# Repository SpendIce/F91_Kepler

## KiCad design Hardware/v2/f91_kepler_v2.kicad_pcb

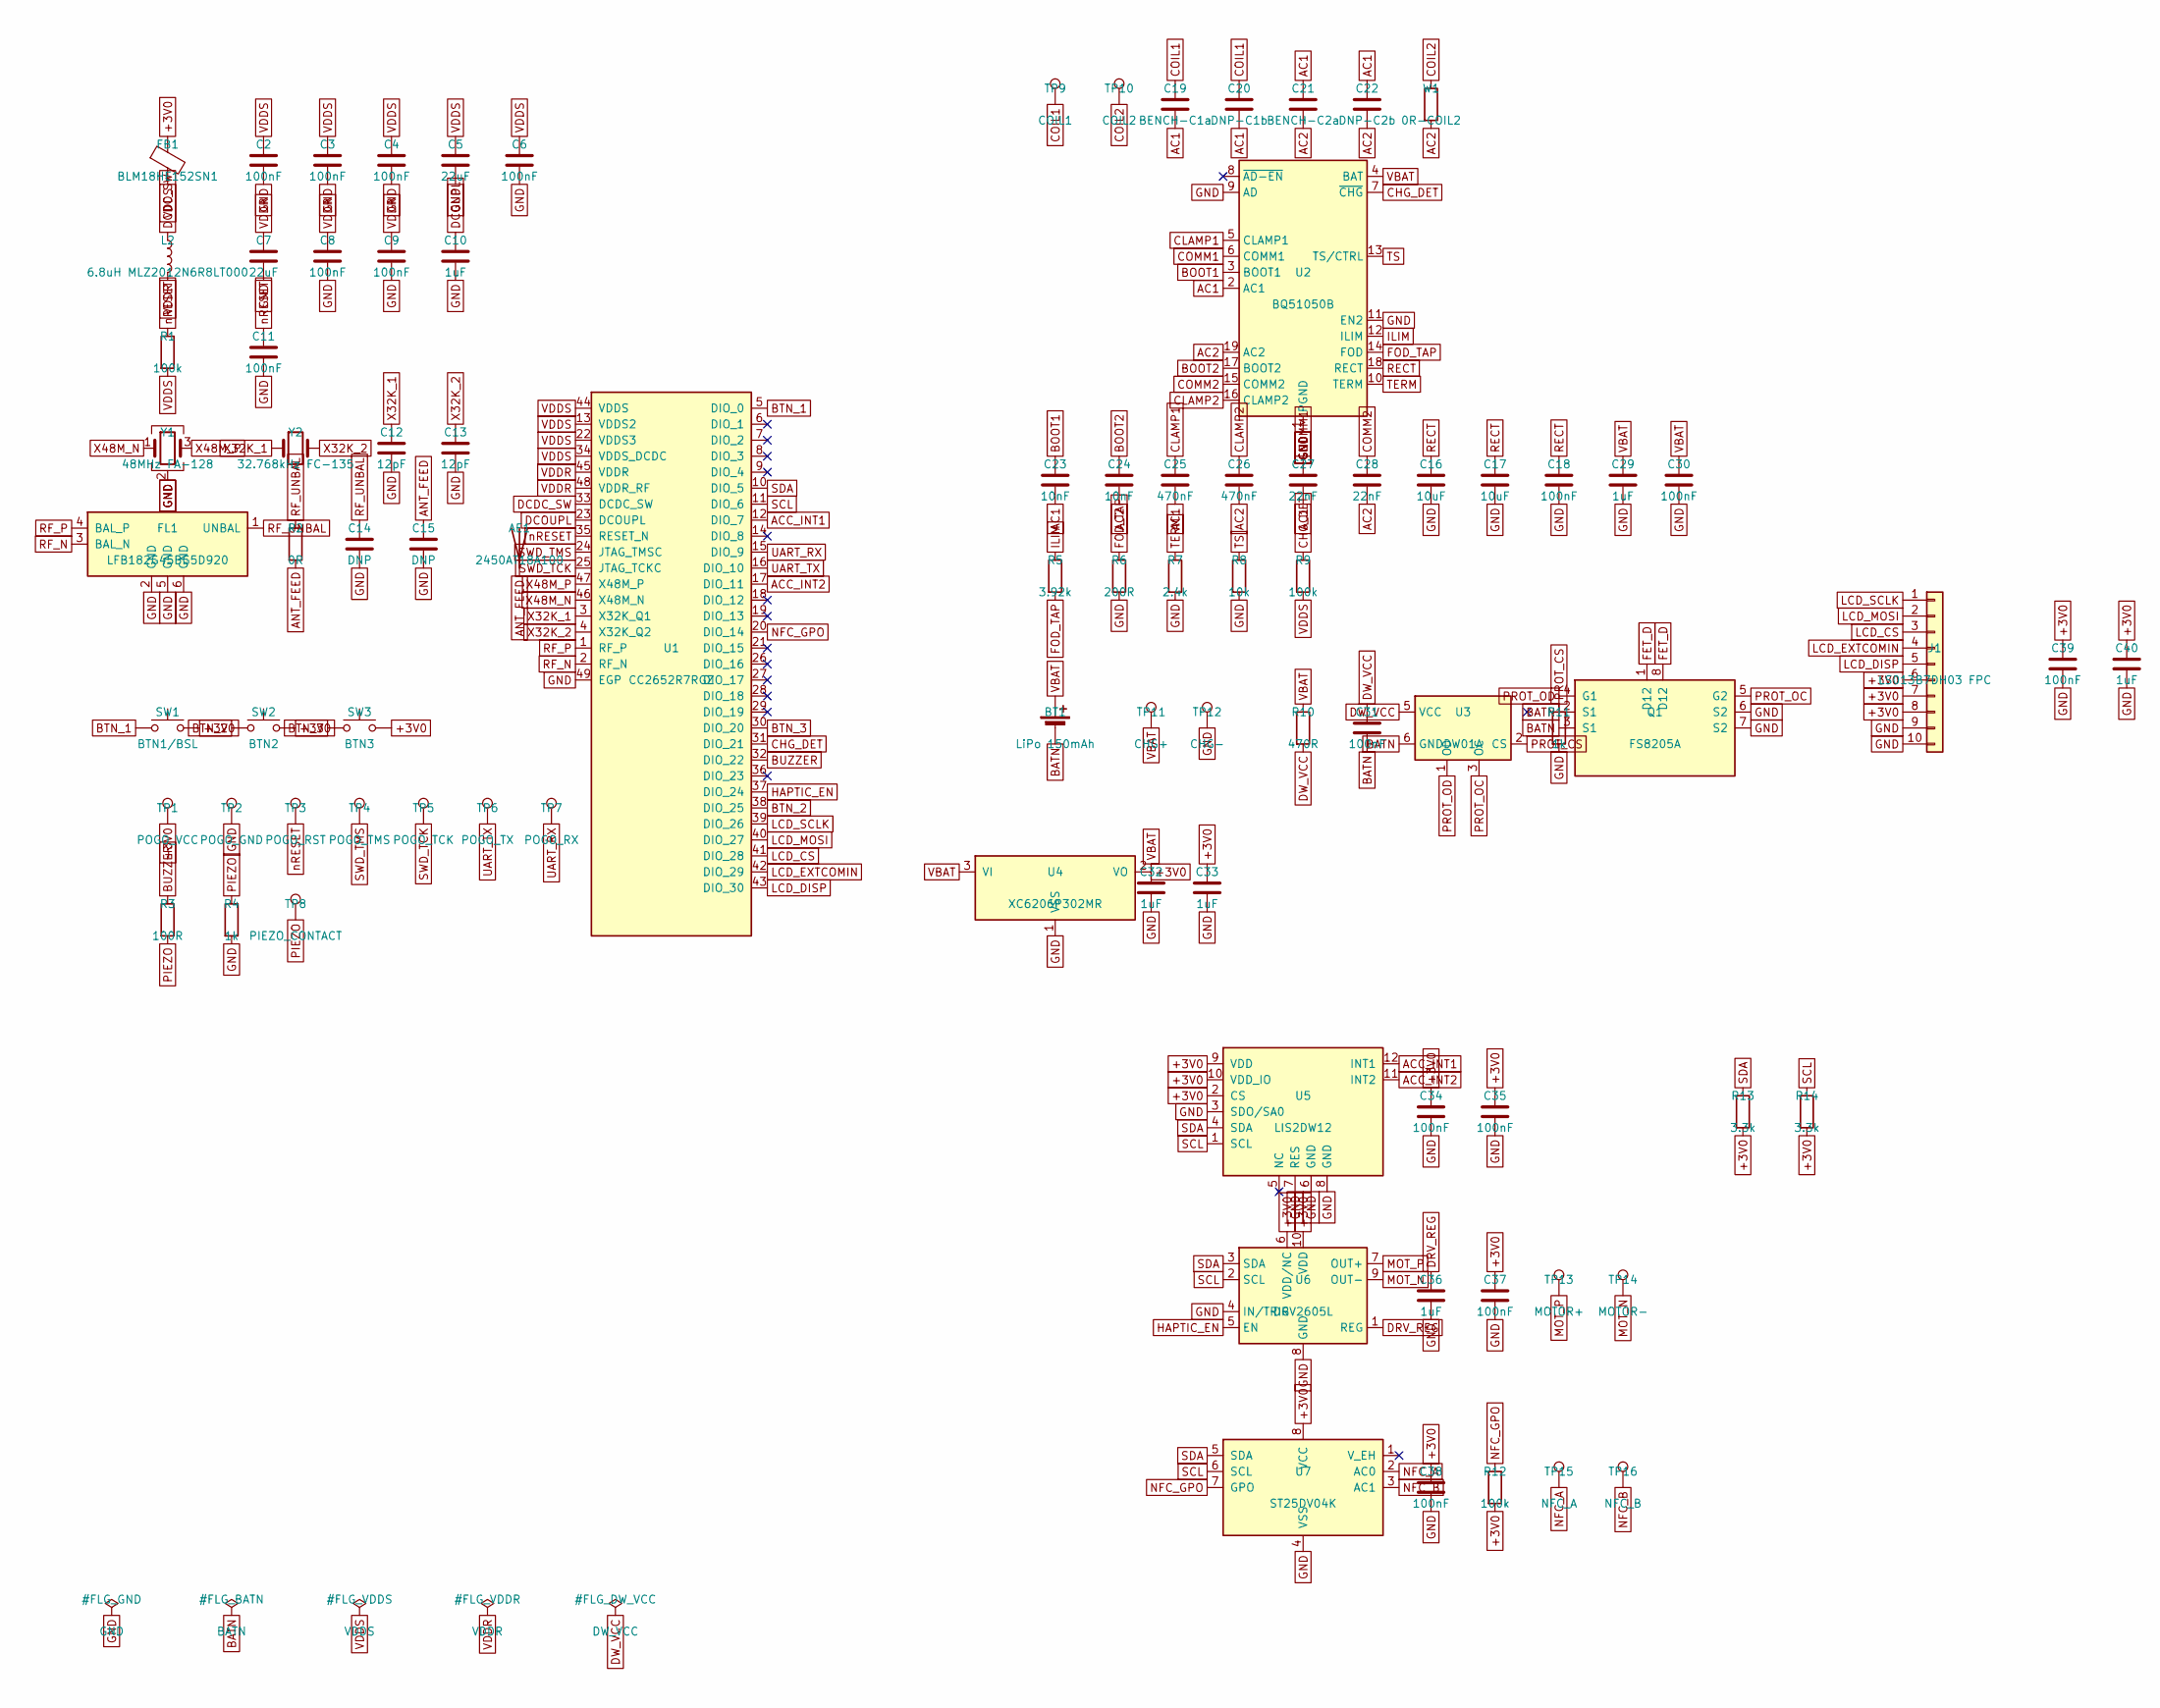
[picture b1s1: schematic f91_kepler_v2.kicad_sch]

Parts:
AE1: 2450AT18A100; ANT_2450AT18A100
BT1: LiPo 150mAh; Back_BatteryPads
C2, C3, C4, C6, C8, C9, C11, C34, C35, C39: 100nF; C_0402_1005Metric
C5, C7: 22uF; C_0603_1608Metric
C10, C40: 1uF; C_0402_1005Metric
C12, C13: 12pF; C_0402_1005Metric
C14, C15: DNP; C_0402_1005Metric
C16, C17: 10uF; Back_C_0603_1608Metric
C18, C30, C31, C37, C38: 100nF; Back_C_0402_1005Metric
C19: BENCH-C1a; Back_C_0603_1608Metric
C20: DNP-C1b; Back_C_0603_1608Metric
C21: BENCH-C2a; Back_C_0402_1005Metric
C22: DNP-C2b; Back_C_0402_1005Metric
C23, C24: 10nF; Back_C_0402_1005Metric
C25, C26: 470nF; Back_C_0402_1005Metric
C27, C28: 22nF; Back_C_0402_1005Metric
C29, C32, C33, C36: 1uF; Back_C_0402_1005Metric
FB1: BLM18HE152SN1; L_0603_1608Metric
FL1: LFB182G45BG5D920; F91_Murata_LFB18_1608
J1: LS013B7DH03 FPC; F91_LCD_FPC_Hirose_FH12-10
L2: 6.8uH MLZ2012N6R8LT000; L_0805_2012Metric
Q1: FS8205A; Back_TSSOP-8_3x3mm_P0.65mm
R1, R9: 100k; R_0402_1005Metric
R2: 0R; R_0402_1005Metric
R3: 100R; R_0402_1005Metric
R4: 1k; R_0402_1005Metric
R5: 3.92k; Back_R_0402_1005Metric
R6: 200R; Back_R_0402_1005Metric
R7: 2.4k; Back_R_0402_1005Metric
R8: 10k; Back_R_0402_1005Metric
R10: 470R; Back_R_0402_1005Metric
R11: 1k; Back_R_0402_1005Metric
R12: 100k; Back_R_0402_1005Metric
R13, R14: 3.3k; Back_R_0402_1005Metric
SW1: BTN1/BSL; SW_Push_1P1T_NO_CK_KMR2
SW2: BTN2; SW_Push_1P1T_NO_CK_KMR2
SW3: BTN3; SW_Push_1P1T_NO_CK_KMR2
TP1: POGO_VCC; Back_TestPoint_Pad_1.5x1.5mm
TP2: POGO_GND; Back_TestPoint_Pad_1.5x1.5mm
TP3: POGO_RST; Back_TestPoint_Pad_1.5x1.5mm
TP4: POGO_TMS; Back_TestPoint_Pad_1.5x1.5mm
TP5: POGO_TCK; Back_TestPoint_Pad_1.5x1.5mm
TP6: POGO_TX; Back_TestPoint_Pad_1.5x1.5mm
TP7: POGO_RX; Back_TestPoint_Pad_1.5x1.5mm
TP8: PIEZO_CONTACT; Back_TestPoint_Pad_1.5x1.5mm
TP9: COIL1; Back_TestPoint_Pad_1.5x1.5mm
TP10: COIL2; Back_TestPoint_Pad_1.5x1.5mm
TP11: CHG+; Back_TestPoint_Pad_1.5x1.5mm
TP12: CHG-; Back_TestPoint_Pad_1.5x1.5mm
TP13: MOTOR+; Back_TestPoint_Pad_1.5x1.5mm
TP14: MOTOR-; Back_TestPoint_Pad_1.5x1.5mm
TP15: NFC_A; Back_TestPoint_Pad_1.5x1.5mm
TP16: NFC_B; Back_TestPoint_Pad_1.5x1.5mm
U1: CC2652R7RGZ; QFN-48-1EP_7x7mm_P0.5mm_EP5.15x5.15mm
U2: BQ51050B; Back_VQFN-20-1EP_4.5x3.5mm_P0.5mm
U3: DW01A; Back_SOT-23-6
U4: XC6206P302MR; Back_SOT-23
U5: LIS2DW12; LGA-12_2x2mm_P0.5mm
U6: DRV2605L; Back_VSSOP-10_3x3mm_P0.5mm
U7: ST25DV04K; Back_SOIC-8_3.9x4.9mm_P1.27mm
W1: 0R-COIL2; Back_R_0402_1005Metric
Y1: 48MHz FA-128; Epson_FA-128_2.0x1.6mm
Y2: 32.768kHz FC-135; Crystal_SMD_3215-2Pin_3.2x1.5mm

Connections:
+3V0: C33.1, C34.1, C35.1, C37.1, C38.1, C39.1, C40.1, FB1.1, J1.6, J1.7, J1.8, R12.2, R13.2, R14.2, SW1.2, SW2.2, SW3.2, TP1.1, U4.2 (VO), U5.2 (CS), U5.9 (VDD), U5.10 (VDD_IO), U6.6 (VDD/NC), U6.10 (VDD), U7.8 (VCC)
AC1: C19.2, C20.2, C21.1, C22.1, C23.2, C25.2, C27.2, U2.2 (AC1)
AC2: C21.2, C22.2, C24.2, C26.2, C28.2, U2.19 (AC2), W1.2
ACC_INT1: U1.12 (DIO_7), U5.12 (INT1)
ACC_INT2: U1.17 (DIO_11), U5.11 (INT2)
ANT_FEED: AE1.1, C15.1, R2.2
BATN: BT1.2 (-), C31.2, Q1.2 (S1), Q1.3 (S1), U3.6 (GND)
BOOT1: C23.1, U2.3 (BOOT1)
BOOT2: C24.1, U2.17 (BOOT2)
BTN_1: SW1.1, U1.5 (DIO_0)
BTN_2: SW2.1, U1.38 (DIO_25)
BTN_3: SW3.1, U1.30 (DIO_20)
BUZZER: R3.1, U1.32 (DIO_22)
CHG_DET: R9.1, U1.31 (DIO_21), U2.7 (~CHG)
CLAMP1: C25.1, U2.5 (CLAMP1)
CLAMP2: C26.1, U2.16 (CLAMP2)
COIL1: C19.1, C20.1, TP9.1
COIL2: TP10.1, W1.1
COMM1: C27.1, U2.6 (COMM1)
COMM2: C28.1, U2.15 (COMM2)
DCDC_SW: L2.1, U1.33 (DCDC_SW)
DCOUPL: C10.1, U1.23 (DCOUPL)
DRV_REG: C36.1, U6.1 (REG)
DW_VCC: C31.1, R10.2, U3.5 (VCC)
FET_D: Q1.1 (D12), Q1.8 (D12)
FOD_TAP: R5.2, R6.1, U2.14 (FOD)
GND: C2.2, C3.2, C4.2, C5.2, C6.2, C7.2, C8.2, C9.2, C10.2, C11.2, C12.2, C13.2, C14.2, C15.2, C16.2, C17.2, C18.2, C29.2, C30.2, C32.2, C33.2, C34.2, C35.2, C36.2, C37.2, C38.2, C39.2, C40.2, FL1.2 (GND), FL1.5 (GND), FL1.6 (GND), J1.9, J1.10, Q1.6 (S2), Q1.7 (S2), R4.2, R6.2, R7.2, R8.2, R11.2, TP2.1, TP12.1, U1.49 (EGP), U2.1 (PGND), U2.9 (AD), U2.11 (EN2), U2.20 (PGND), U2.21 (PGND), U4.1 (VSS), U5.3 (SDO/SA0), U5.6 (GND), U5.7 (RES), U5.8 (GND), U6.4 (IN/TRIG), U6.8 (GND), U7.4 (VSS), Y1.2 (G), Y1.4 (G)
HAPTIC_EN: U1.37 (DIO_24), U6.5 (EN)
ILIM: R5.1, U2.12 (ILIM)
LCD_CS: J1.3, U1.41 (DIO_28)
LCD_DISP: J1.5, U1.43 (DIO_30)
LCD_EXTCOMIN: J1.4, U1.42 (DIO_29)
LCD_MOSI: J1.2, U1.40 (DIO_27)
LCD_SCLK: J1.1, U1.39 (DIO_26)
MOT_N: TP14.1, U6.9 (OUT-)
MOT_P: TP13.1, U6.7 (OUT+)
NFC_A: TP15.1, U7.2 (AC0)
NFC_B: TP16.1, U7.3 (AC1)
NFC_GPO: R12.1, U1.20 (DIO_14), U7.7 (GPO)
PIEZO: R3.2, R4.1, TP8.1
PROT_CS: R11.1, U3.2 (CS)
PROT_OC: Q1.5 (G2), U3.3 (OC)
PROT_OD: Q1.4 (G1), U3.1 (OD)
RECT: C16.1, C17.1, C18.1, U2.18 (RECT)
RF_N: FL1.3 (BAL_N), U1.2 (RF_N)
RF_P: FL1.4 (BAL_P), U1.1 (RF_P)
RF_UNBAL: C14.1, FL1.1 (UNBAL), R2.1
SCL: R14.1, U1.11 (DIO_6), U5.1 (SCL), U6.2 (SCL), U7.6 (SCL)
SDA: R13.1, U1.10 (DIO_5), U5.4 (SDA), U6.3 (SDA), U7.5 (SDA)
SWD_TCK: TP5.1, U1.25 (JTAG_TCKC)
SWD_TMS: TP4.1, U1.24 (JTAG_TMSC)
TERM: R7.1, U2.10 (TERM)
TS: R8.1, U2.13 (TS/CTRL)
UART_RX: TP7.1, U1.15 (DIO_9)
UART_TX: TP6.1, U1.16 (DIO_10)
VBAT: BT1.1 (+), C29.1, C30.1, C32.1, R10.1, TP11.1, U2.4 (BAT), U4.3 (VI)
VDDR: C7.1, C8.1, C9.1, L2.2, U1.45 (VDDR), U1.48 (VDDR_RF)
VDDS: C2.1, C3.1, C4.1, C5.1, C6.1, FB1.2, R1.2, R9.2, U1.13 (VDDS2), U1.22 (VDDS3), U1.34 (VDDS_DCDC), U1.44 (VDDS)
X32K_1: C12.1, U1.3 (X32K_Q1), Y2.1
X32K_2: C13.1, U1.4 (X32K_Q2), Y2.2
X48M_N: U1.46 (X48M_N), Y1.1
X48M_P: U1.47 (X48M_P), Y1.3
nRESET: C11.1, R1.1, TP3.1, U1.35 (RESET_N)

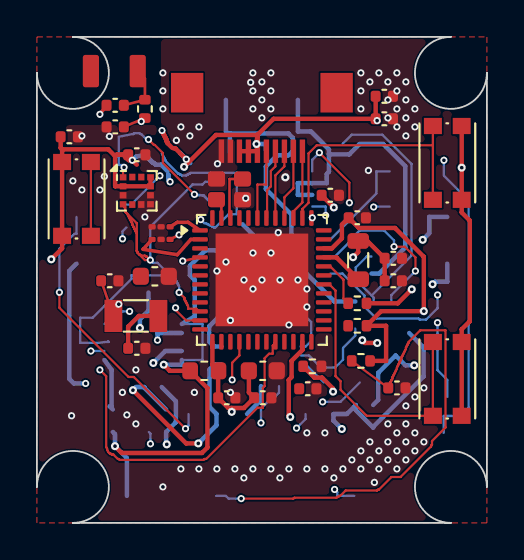
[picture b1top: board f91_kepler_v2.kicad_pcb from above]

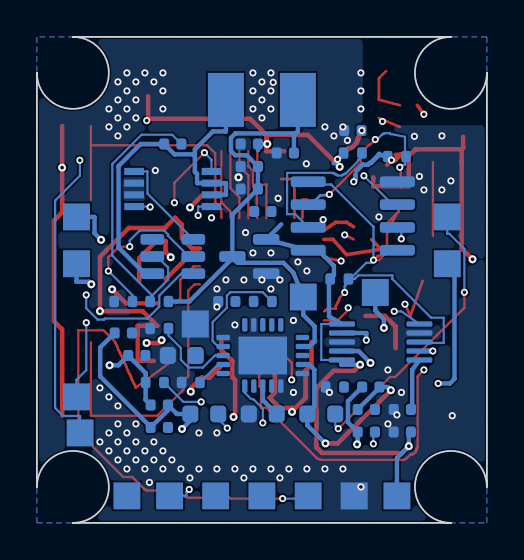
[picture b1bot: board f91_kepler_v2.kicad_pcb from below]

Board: 4 copper layers, 25.0 x 27.0 mm, 89 parts (54 on the bottom side), 63 nets.

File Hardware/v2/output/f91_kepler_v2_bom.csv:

"Reference","Value","Footprint","QUANTITY","DNP"
"AE1","PCB-IFA (v1 geometry)","f91_footprints:ANT_v1_IFA","1",""
"BT1","LiPo 150mAh","f91_footprints:BatteryPads","1",""
"C2-C4,C6,C8,C9,C11,C18,C30,C31,C34,C35,C37-C39","100nF","Capacitor_SMD:C_0402_1005Metric","15",""
"C5,C7","22uF","Capacitor_SMD:C_0603_1608Metric","2",""
"C10,C29,C32,C33,C36,C40","1uF","Capacitor_SMD:C_0402_1005Metric","6",""
"C12,C13","12pF","Capacitor_SMD:C_0402_1005Metric","2",""
"C14,C15","DNP","Capacitor_SMD:C_0402_1005Metric","2",""
"C16,C17","10uF","Capacitor_SMD:C_0603_1608Metric","2",""
"C19","BENCH-C1a","Capacitor_SMD:C_0603_1608Metric","1",""
"C20","DNP-C1b","Capacitor_SMD:C_0603_1608Metric","1",""
"C21","BENCH-C2a","Capacitor_SMD:C_0402_1005Metric","1",""
"C22","DNP-C2b","Capacitor_SMD:C_0402_1005Metric","1",""
"C23,C24","10nF","Capacitor_SMD:C_0402_1005Metric","2",""
"C25,C26","470nF","Capacitor_SMD:C_0402_1005Metric","2",""
"C27,C28","22nF","Capacitor_SMD:C_0402_1005Metric","2",""
"FB1","BLM18HE152SN1","Inductor_SMD:L_0603_1608Metric","1",""
"FL1","LFB182G45BG5D920","f91_footprints:Murata_LFB18_1608","1",""
"J1","LS013B7DH03 FPC","Connector_FFC-FPC:Hirose_FH12-10S-0.5SH_1x10-1MP_P0.50mm_Horizontal","1",""
"L2","6.8uH MLZ2012N6R8LT000","Inductor_SMD:L_0805_2012Metric","1",""
"Q1","FS8205A","Package_SO:TSSOP-8_3x3mm_P0.65mm","1",""
"R1,R9,R12","100k","Resistor_SMD:R_0402_1005Metric","3",""
"R2","0R","Resistor_SMD:R_0402_1005Metric","1",""
"R3","100R","Resistor_SMD:R_0402_1005Metric","1",""
"R4,R11","1k","Resistor_SMD:R_0402_1005Metric","2",""
"R5","3.92k","Resistor_SMD:R_0402_1005Metric","1",""
"R6","200R","Resistor_SMD:R_0402_1005Metric","1",""
"R7","2.4k","Resistor_SMD:R_0402_1005Metric","1",""
"R8","10k","Resistor_SMD:R_0402_1005Metric","1",""
"R10","470R","Resistor_SMD:R_0402_1005Metric","1",""
"R13,R14","3.3k","Resistor_SMD:R_0402_1005Metric","2",""
"SW1","BTN1/BSL","Button_Switch_SMD:SW_Push_1P1T_NO_CK_KMR2","1",""
"SW2","BTN2","Button_Switch_SMD:SW_Push_1P1T_NO_CK_KMR2","1",""
"SW3","BTN3","Button_Switch_SMD:SW_Push_1P1T_NO_CK_KMR2","1",""
"TP1","POGO_VCC","TestPoint:TestPoint_Pad_1.5x1.5mm","1",""
"TP2","POGO_GND","TestPoint:TestPoint_Pad_1.5x1.5mm","1",""
"TP3","POGO_RST","TestPoint:TestPoint_Pad_1.5x1.5mm","1",""
"TP4","POGO_TMS","TestPoint:TestPoint_Pad_1.5x1.5mm","1",""
"TP5","POGO_TCK","TestPoint:TestPoint_Pad_1.5x1.5mm","1",""
"TP6","POGO_TX","TestPoint:TestPoint_Pad_1.5x1.5mm","1",""
"TP7","POGO_RX","TestPoint:TestPoint_Pad_1.5x1.5mm","1",""
"TP8","PIEZO_CONTACT","TestPoint:TestPoint_Pad_1.5x1.5mm","1",""
"TP9","COIL1","TestPoint:TestPoint_Pad_1.5x1.5mm","1",""
"TP10","COIL2","TestPoint:TestPoint_Pad_1.5x1.5mm","1",""
"TP11","CHG+","TestPoint:TestPoint_Pad_1.5x1.5mm","1",""
"TP12","CHG-","TestPoint:TestPoint_Pad_1.5x1.5mm","1",""
"TP13","MOTOR+","TestPoint:TestPoint_Pad_1.5x1.5mm","1",""
"TP14","MOTOR-","TestPoint:TestPoint_Pad_1.5x1.5mm","1",""
"TP15","NFC_A","TestPoint:TestPoint_Pad_1.5x1.5mm","1",""
"TP16","NFC_B","TestPoint:TestPoint_Pad_1.5x1.5mm","1",""
"U1","CC2652R7RGZ","Package_DFN_QFN:QFN-48-1EP_7x7mm_P0.5mm_EP5.15x5.15mm","1",""
"U2","BQ51050B","f91_footprints:VQFN-20-1EP_4.5x3.5mm_P0.5mm","1",""
"U3","DW01A","Package_TO_SOT_SMD:SOT-23-6","1",""
"U4","XC6206P302MR","Package_TO_SOT_SMD:SOT-23","1",""
"U5","LIS2DW12","Package_LGA:LGA-12_2x2mm_P0.5mm","1",""
"U6","DRV2605L","f91_footprints:VSSOP-10_3x3mm_P0.5mm","1",""
"U7","ST25DV04K","Package_SO:SOIC-8_3.9x4.9mm_P1.27mm","1",""
"W1","0R-COIL2","Resistor_SMD:R_0402_1005Metric","1",""
"Y1","48MHz FA-128","f91_footprints:Crystal_SMD_3215-4Pin_3.2x1.5mm","1",""
"Y2","32.768kHz FC-135","Crystal:Crystal_SMD_3215-2Pin_3.2x1.5mm","1",""

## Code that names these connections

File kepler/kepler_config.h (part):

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  #define KEPLER_V2_ACC_INT2_PIN    IOID_11   /* pad 17 — LIS2DW12 INT2    */
  #define KEPLER_V2_NFC_GPO_PIN     IOID_14   /* pad 20 — ST25DV GPO       */
  #define KEPLER_V2_CHG_DET_PIN     IOID_21   /* pad 31 — Qi charge detect */
  #define KEPLER_V2_BUZZER_PIN      IOID_22   /* pad 32 — piezo PWM        */
  #define KEPLER_V2_HAPTIC_EN_PIN   IOID_24   /* pad 37 — DRV2605L EN      */
#endif /* KEPLER_BOARD_V2 */

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#define KEPLER_LIS2DW12_INT2_PIN    IOID_UNUSED   /* Accelerometer interrupt 2    */
#define KEPLER_ST25DV_GPO_PIN       IOID_UNUSED   /* NFC tag GPO interrupt        */
#define KEPLER_INDUCTIVE_CHG_PIN    IOID_UNUSED   /* Inductive charge detection   */
#define KEPLER_BUZZER_PWM_PIN       IOID_UNUSED   /* Piezo buzzer PWM output      */
#define KEPLER_BUZZER_PWM_INDEX     0             /* TI PWM driver instance       */

/*==========================================================================*
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#define KEPLER_HAS_INDUCTIVE_CHG    0   /* Enable when charge coil present  */
#endif
#ifndef KEPLER_HAS_BUZZER
#define KEPLER_HAS_BUZZER           0   /* Enable once the v1 buzzer trace  *
                                         * is verified and the PWM pin set  */
#endif

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
#define KEPLER_SCREEN_COUNT                 6      /* MAIN, WEATHER, NOTIF, LOCATOR, STOPWATCH, ALARMS */
#define KEPLER_SCREEN_TIMEOUT_MS            8000   /* Auto-return to MAIN after inactivity   */
#define KEPLER_INVERT_DISPLAY_DURATION_MS   3000   /* BTN_1 long-press: invert for 3 s       */

/*==========================================================================*
 *  NOTIFICATION RING BUFFER                                               *
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
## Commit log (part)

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2026-03-18 Add project docs and kepler/ module skeleton
2026-03-21 lcd screen firmware and buttons
2026-06-09 docs: add Codex operating guide
2026-06-09 docs: organize project planning
2026-06-10 feat(core): event queue, NV flash store, shared types, I2C bus helper
    Foundation for Phase 0 tasks 3-6: central kepler_event_t queue (static
    ring + counting semaphore, Hwi-safe post), osal_snv-backed key-value
    store with safe defaults, shared BLE/NV payload structs, and a single
    shared I2C bus owner for DRV2605L/LIS2DW12/ST25DV. Feature flags in
    kepler_config.h are now #ifndef-guarded so test and CCS configurations
    can override them per build.
2026-06-10 feat(haptic): DRV2605L driver and vibration patterns (Task 3)
    I2C driver for the DRV2605L: device probe via STATUS ID, ERM library 1,
    one-time auto-calibration persisted to NV (reloaded on later boots),
    standby between events. Named patterns map notification types to
    waveform sequences; HAPTIC_CALL repeats via a 500 ms clock that posts
    EVT_HAPTIC_TICK so the GO retrigger runs in task context (no I2C in
    Swi). All code stubs away cleanly with KEPLER_HAS_DRV2605L=0.
2026-06-10 feat(power,ble,audio): power manager, BLE services, buzzer, input wake hooks (Task 5)
    Power manager owns the screen inactivity clock (posts EVT_SCREEN_TIMEOUT)
    and battery readout. BLE manager implements the advertising policy
    (fast 100 ms for 30 s, then slow 2 s; off while connected) behind a
    ble_port_t function table so the GAP calls stay in the legacy CCS app
    and the logic is host-testable. Notification service parses 0xFF01/02/05
    writes into queue events with a 4-slot static pool, and pushes step
2026-06-10 feat(screens): weather, alarms, locator, stopwatch, icons, main event loop (Task 6)
    Weather service owns the authoritative weather_data_s the renderer
    forward-declared in Task 1 (wire payload persisted in Celsius, UI copy
    pre-converted to the display unit) and the 0xFF0A refresh notify.
    Alarm service syncs up to 5 read-mostly alarms with watch-side toggle
    written back by notifying 0xFF08. Locator drives 0xFF07 start/stop
    with 30 s auto-stop and 1 Hz blink. Stopwatch runs a 10 ms clock only
2026-06-10 test: host suites for tasks 3-6 with I2C/PWM/SNV/RTOS stubs
    New stubs: register-file I2C mock (with device-behaviour write hook),
    PWM recorder, RAM-backed osal_snv, Semaphore/Hwi/Task/BIOS. Suites
    cover DRV2605L calibration paths and pattern repeat, LIS2DW12 register
    sequences, pedometer rollover and crash recovery, actigraphy epochs and
    window logic, event queue FIFO/overflow, flash defaults and rotation,
    advertising policy, notification parsing, buzzer sequencing, weather/
2026-06-10 test: build and run all six host suites (214 assertions green)
    User authorized lifting the no-build rule for host tests this session.
    Fixes surfaced by compiling:
    - time_set.c: gmtime_r needs _POSIX_C_SOURCE when built with host glibc
    (guarded to not affect the TI toolchain)
    - test_task1.c: define mock_seconds_value and extend the link line —
    ui_renderer now pulls Seconds + weather/alarm services (Task 6)
2026-06-11 fix(app): lowercase Board.h/OSAL.h includes for case-sensitive filesystems
    SDK 4.40 ships board.h and osal.h lowercase; uppercase includes only
    resolved on Windows. Required to build baseline firmware on Linux.
2026-06-11 fix(target): Seconds.h lives at ti/sysbios/hal, not ti/drivers
    The TI-RTOS Seconds module header path used by the real SDK (and by the
    original f91_clock.c) is <ti/sysbios/hal/Seconds.h>. All kepler sources
    and the host stub now use it — integration with the CCS project would
    have failed on the first compile otherwise. All six suites rerun green.
2026-06-11 fix(target),perf(ram): drop libc time deps, trim queues/buffers for R1
    TI's runtime has no gmtime_r and its mktime drags TZ machinery — the
    first CCS link failed on it. New kepler_time.c does epoch<->civil
    conversion locally (Hinnant civil_from_days, also dedupes the copy that
    lived in kepler_main) and kepler_epoch_set_hm replaces the
    gmtime_r+mktime round trip in time_set.
    RAM trims toward the R1 gate, all measured on TI CGT objects:
2026-06-11 feat(app): link kepler/ modules into the CCS build (Phase 0 integration)
    - .project: link the repo-root kepler/ folder into the app project
    - .cproject (both configs): repo-root include path, exclude kepler/test
    and the replaced legacy sources (ssd1306.c, f91_buttons.c), define
    BOARD_DISPLAY_SHARP_SIZE=16 and BOARD_DISPLAY_UART_STRBUF_SIZE=32 to
    shrink dead SDK Display buffers (the unconditional sharpDisplayBuf
    alone wasted 2 KB of SRAM with BOARD_DISPLAY_USE_LCD=0)
2026-06-11 docs(phase2): PCB v2 fabrication readiness package
    Decision sheet + BOM delta + pin map + layout constraints + JLCPCB
    order spec for Fase 2. Includes a Plan Maestro erratum with evidence:
    the v1 MCU is CC2640R2FRGZR (VQFN-48 7x7, per BOM and the IOID_25/26
    button mapping), not the QFN-32 4x4 the plan claims — which reopens
    the CC2652R7 upgrade path on the same footprint class. Records the
    measured R1/R2 gate state: flash passed (102.8/124 KB dual-resident),
2026-06-11 docs(phase2): record MCU decision — CC2652R7, OAD dual-image in scope
    Option B chosen. Internal-flash dual-image OAD fits (~300 KB per slot
    after the BLE5 stack), external SPI NOR demoted to optional. Firmware
    retargets SimpleLink SDK 7.x/BLE5-Stack: PIN->GPIO shims needed in the
    three pin-touching modules, fresh 0xFFFF GATT service on a basic_ble
    example instead of migrating the legacy FA35xxxx layer. Bring-up board:
    LP-CC2652R7. RF matching from the LP reference design, not from v1.
2026-06-11 feat(tools): ESP32 peripheral test rig — kepler sources unchanged
    Compiles the kepler/ drivers (LCD, haptic, accel, services) on a plain
    ESP32-WROOM devkit through a TI-API shim layer: ti/drivers PIN/SPI/I2C
    and ti/sysbios Clock/Task/Semaphore/Hwi/Seconds + osal_snv mapped onto
    ESP-IDF spi_master, i2c, esp_timer, FreeRTOS and NVS. No kepler source
    changes — same include paths, IOID pins translated through one table in
    rig_config.h.
2026-06-11 docs(phase2): lean assembly path — BSL/UART flashing, PCBA, no LaunchPad
    Programming moves to the CC2652R7 ROM serial bootloader over UART
    (CP2102 + cc2538-bsl), backdoor on a button, OAD after first flash;
    pogo pads grow to 7 (UART TX/RX added), SWD kept as escape hatch.
    Assembly: JLCPCB economic PCBA, 2 of 5 boards populated, single-side
    SMT target. Wireless charging (BQ51013B + coil) stays on the first run
    by user decision; only the NFC tag (ST25DV) is DNP with routed pads.
2026-06-11 docs(phase2): populate ST25DV NFC from the first assembly run
    User decision: avoid hand-soldering later; full BOM assembled, nothing
    DNP. Budget impact ~US$2/board.
2026-06-12 feat(port): SDK 7.x port skeleton for CC2652R7 — PIN shim, 0xFFFF GATT service, ble_port glue
    - pin_shim: PIN-over-GPIO translation (PIN driver removed in SDK 7.x);
    buttons.c / sharp_lcd.c / wrist_raise.c port unchanged
    - kepler_gatt_service: BLE5-Stack attribute table for the spec 0xFFFF
    service, 10 characteristics FF01-FF0A with CCCDs, exact-length write
    validation routing into kepler_ble_on_char_write
    - kepler_ble_port: ble_port_t over GapAdv_*, GAP link-event forwarding,
2026-06-13 feat(hw): KiCad v2 schematic — CC2652R7 smartwatch, ERC clean
    Generated schematic for the CC2652R7 board: programmatic netlist
    (tools/netlist.py) -> global-label schematic (gen_schematic.py), custom
    symbols (gen_symbols.py). ERC: 0 errors, 2 understood warnings
    (XC6206 flatten artifact; LIS2DW12 SA0->GND I2C-0x18 strap).
    Blocks: CC2652R7 + RF (Murata LFB18 balun, 48MHz/32k crystals, internal
    DCDC, decoupling per TI SWRA640/zzh ref), BQ51050B Qi rx + integrated
2026-06-13 feat(hw): v2 PCB layout starting point + layout guide
    gen_pcb.py builds f91_kepler_v2.kicad_pcb via the pcbnew API: all 89
    footprints loaded + placed (rough spread) with the full netlist assigned
    (202-connection ratsnest), 2-layer / 1.0mm stackup, JLCPCB design rules
    (0.127mm track/space, 0.45/0.3 via), 30x28mm placeholder outline.
    DRC on the unrouted board: only expected unconnected + spread-overlap
    clearance, no structural errors.
2026-06-27 feat(hw/v2): fix5.py — second-pass DRC short elimination
    Fixes 10 root-cause short clusters surviving fix4.py:
    - Y2 (32kHz XTAL): right pad was inside U1 5.6×5.6mm GND thermal pad; move to (7.0,14.5)
    - R13 I2C pullup: was at x=9.0 inside U1 left-pad copper; move to x=6.5
    - C19-C22 (Qi AC caps): placed on Y1 crystal by fix4; move to ROW y=21.0/24.1 at x=10/12.5
    - Qi bypass grid: shift left column from x=17.5 to x=13.0 (was hitting U2 AC1 at x=17.3)
    - BT1 connector: ±2mm pad pitch puts VBAT pad at y=24.5 shorting TP3; move to (5.0,20.5)
2026-06-27 feat(hw/v2): geometry-driven placement engine — 0 copper shorts
    Replace the fix2..fix5 hand-coordinate approach (could not converge on a
    25x27mm / 89-footprint board) with a single authoritative placement engine
    that uses real pad geometry headlessly.
    Results (kicd-cli DRC, severity-error):
    - shorting_items 78 -> 0
    - solder_mask_bridge 88 -> 0
2026-06-27 feat(hw/v2): connectivity-aware placement optimizer — 30% less wirelength
    Extend place_engine.py with force-directed refinement: each pass pulls every
    movable part toward the centroid of its signal-net neighbours (power/ground
    nets excluded — they get poured), re-places collision-free, and keeps the
    lowest-wirelength layout that still places all 89 parts. Annealed pull
    strength (alpha 0.6->0.12) with 0-fail acceptance; board saved on each
    accepted best.
2026-06-27 feat(hw/v2): RF-lock balun + series-R for short diff pair
    FL1 balun was 6 mm below U1's RF pins (RF_P/RF_N), forcing a long, zigzag
    2.4 GHz differential run. Lock FL1 at (7.4,10.9) rot270 — hugging U1 RF_P@
    (9.06,10.75)/RF_N@(9.06,11.25), polarity matched so the pair doesn't cross —
    and R2 (0R series) at (5.0,12.0) on the straight U1->antenna path to AE1.
    Diff-pair length 6 mm -> RF_P 2.04 mm / RF_N 1.32 mm. FL1/R2 excluded from
    the force-directed drift (RF correctness over global wirelength: HPWL 597->
2026-06-27 fix(hw/v2): L2 stranded off-board at origin; lock it to DCDC_SW pin
    L2 (DCDC inductor) was sitting at (0,0) — fully off-board, copper at x=-1.5.
    Cause: L2's only nets are DCDC_SW + VDDR, both in the power-exclusion set, so
    it had 0 signal degree and sorted dead-last; no free slot remained, and
    half_extents() parks parts at origin to measure -> a failed placement left it
    there. DRC's arc check missed it (copper far from any edge).
    Fixes:
2026-06-27 fix(hw/v2): sync AE1 schematic symbol to chip antenna
    Update AE1 in the schematic to match the PCB chip-antenna swap:
    - Value: "PCB-IFA (v1 geometry)" -> "2450AT18A100"
    - Footprint: f91_footprints:ANT_v1_IFA -> f91_footprints:ANT_2450AT18A100
    Device:Antenna symbol kept (pin1 = Feed = ANT_FEED, matches board pad1);
    footprint pad2 (NC) is an unmapped mechanical pad, which KiCad allows.
    schematic-parity: AE1 has no net conflict. The remaining parity items
